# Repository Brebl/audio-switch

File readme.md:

# Audio switch   

This is an avr project for selecting one audio signal from multiple input lines (6-port maximum). The project is designed to minimize power consumption by making use of sleep modes, interrupts and internal timers. Other features include multifunction pushbutton, LCD, SPI-communication, automatic detection of audio signals via ADC.\
Objective for this project is to generate amazing sound with minimal distortion.

## Layout

4-port setup with HD44780 display, installed in 3.5" FDD mounting bracket.\

## Code / operation

Microcontroller unit detects via analog-to-digital converter what audio lines are receiving signal. MCU sends this information through Serial peripheral interface to the primary MCU and based on input port priority, primary MCU switches on correct input port. Port information is shown in LCD. After 10 secs or so, display turn off to save power. Display is accessed using 4-bit interface. Pushbutton can be used to force certain port open or to switch back to automatic operation.
  
In addition to Master, there's 3 git branches. Each for a different version of this project.
- led_version
- display_version
- automatic_version

To get this running you can use a toolchain
```
avr-libc gcc-avr binutils-avr avrdude
```

For to flash your MCU, run
```shell
make fuses
make flash
```

## Hardware  

Primary MCU is Atmel's Attiny4313 MCU, with internal 128 kHz oscillator. ISP programmer needs to be slowed down because of this low power oscillator. (avrdude -B option) Secondary MCU is Attiny24A. Switching is done by 4066B CMOS Quad Bilateral Switch.
This pcb feature a 10-pin male ISP connector for programming/debugging. Powering this device could be made through USB or with 5V regulator you can use for example 9-volt battery. Board is designed using KiCad software.

### Board

Here's my printed circuit board I ordered from a fabricator pcbway.com\

First test setup with "a proper pcb". Works nice.\

### Electrical charecteristics

Voltage: 5V\
Current: 0,11mA\
Audio connection: max 6x stereo in, 1x stereo out

### Roadmap

- [x] Consept testing with Attiny2313A/4313
- [x] Sleep modes, interrupts
- [x] Simple pushbutton logic
- [x] LED interface
- [x] Schematics
- [x] Design PCB & place order
- [x] Board test setup, sound input/output
- [x] Fabricate enclosure
- [x] Power source
- [x] LCD interface
- [X] ATtiny24A with ADC
- [x] SPI communication 
- [x] Automatic audio signal detection
- [x] Multifunction pushbutton
- [ ] Measure distortion

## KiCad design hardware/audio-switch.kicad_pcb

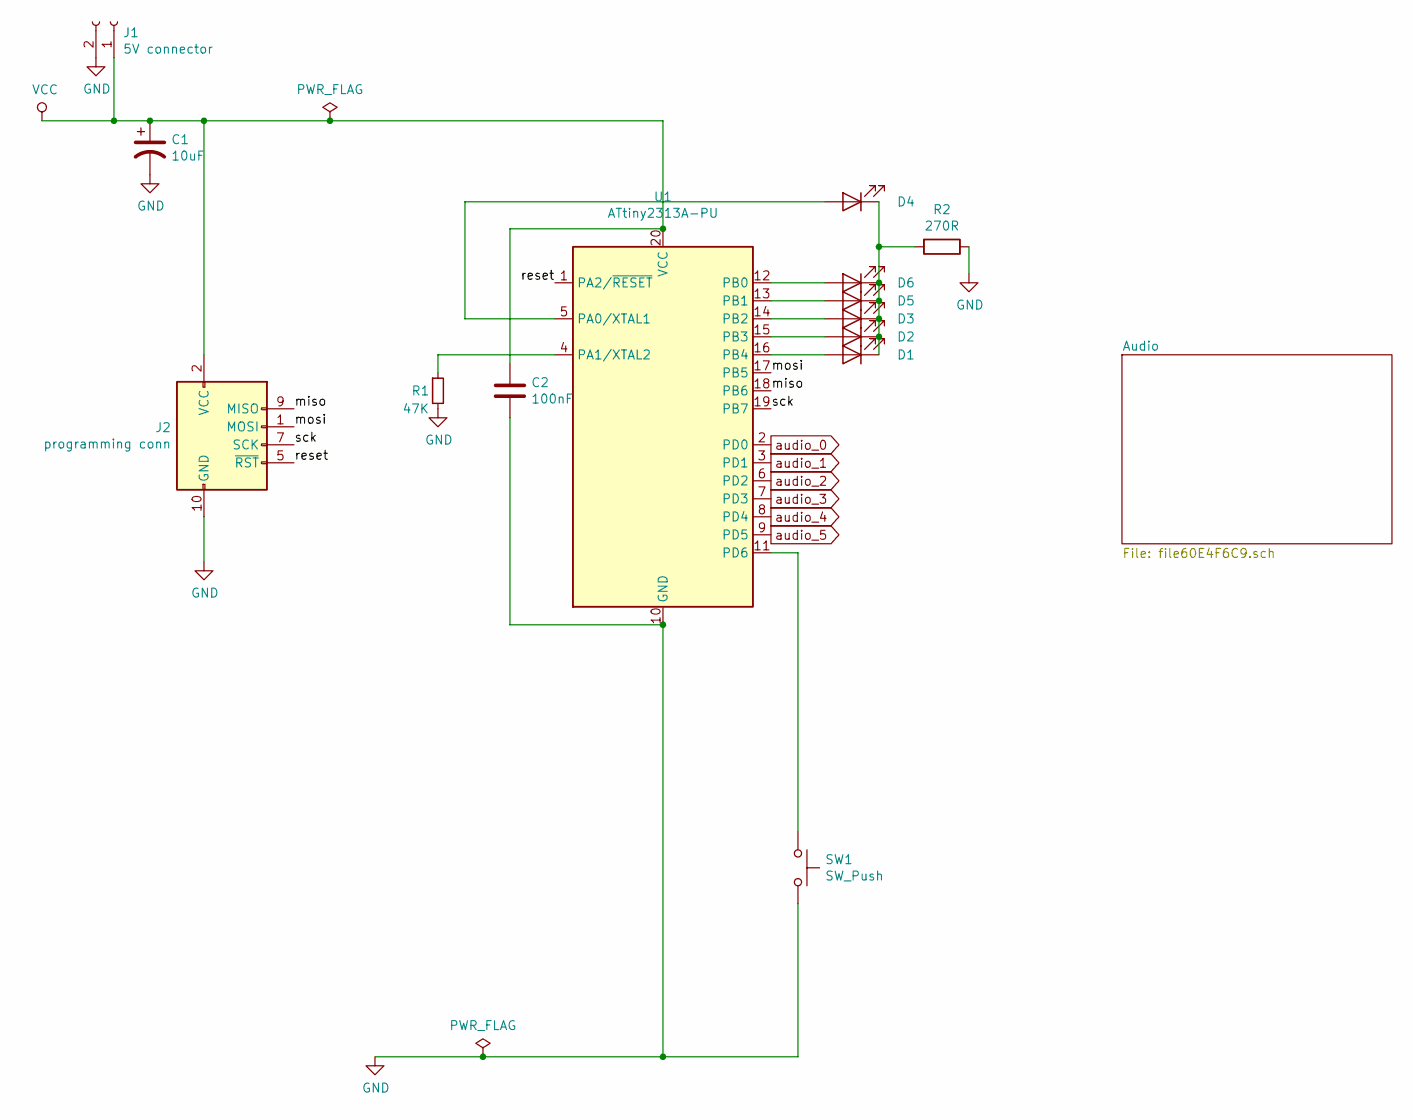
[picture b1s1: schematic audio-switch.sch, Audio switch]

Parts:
C1: 10uF; CP_Radial_D4.0mm_P1.50mm
C2: 100nF; CP_Radial_D5.0mm_P2.00mm
D1, D2, D3, D4, D5, D6: LED; LED_D3.0mm
J1: 5V connector; SolderWirePad_1x02_P3.81mm_Drill1mm
J2: programming conn; PinHeader_2x05_P2.54mm_Vertical
R1: 47K; R_Axial_DIN0207_L6.3mm_D2.5mm_P7.62mm_Horizontal
R2: 270R; R_Axial_DIN0207_L6.3mm_D2.5mm_P7.62mm_Horizontal
SW1: SW_Push; SolderWirePad_1x02_P3.81mm_Drill1mm
U1: ATtiny2313A-PU; DIP-20_W7.62mm

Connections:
/miso: J2.9 (MISO), U1.18 (PB6)
/mosi: J2.1 (MOSI), U1.17 (PB5)
/reset: J2.5 (~RST), U1.1 (PA2/~RESET)
/sck: J2.7 (SCK), U1.19 (PB7)
GND: C1.2, C2.2, J1.2, J2.4 (GND), J2.6 (GND), J2.8 (GND), J2.10 (GND), R1.2, R2.1, SW1.2, U1.10 (GND); also elsewhere on the board
unnamed: D1.1 (K), D2.1 (K), D3.1 (K), D4.1 (K), D5.1 (K), D6.1 (K), R2.2
unnamed: D1.2 (A), U1.16 (PB4)
unnamed: D2.2 (A), U1.15 (PB3)
unnamed: D3.2 (A), U1.14 (PB2)
unnamed: D4.2 (A), U1.5 (PA0/XTAL1)
unnamed: D5.2 (A), U1.13 (PB1)
unnamed: D6.2 (A), U1.12 (PB0)
unnamed: R1.1, U1.4 (PA1/XTAL2)
unnamed: SW1.1, U1.11 (PD6)
VCC: C1.1, C2.1, J1.1, J2.2 (VCC), U1.20 (VCC); also elsewhere on the board
audio_0: U1.2 (PD0); also elsewhere on the board
audio_1: U1.3 (PD1); also elsewhere on the board
audio_2: U1.6 (PD2); also elsewhere on the board
audio_3: U1.7 (PD3); also elsewhere on the board
audio_4: U1.8 (PD4); also elsewhere on the board
audio_5: U1.9 (PD5); also elsewhere on the board

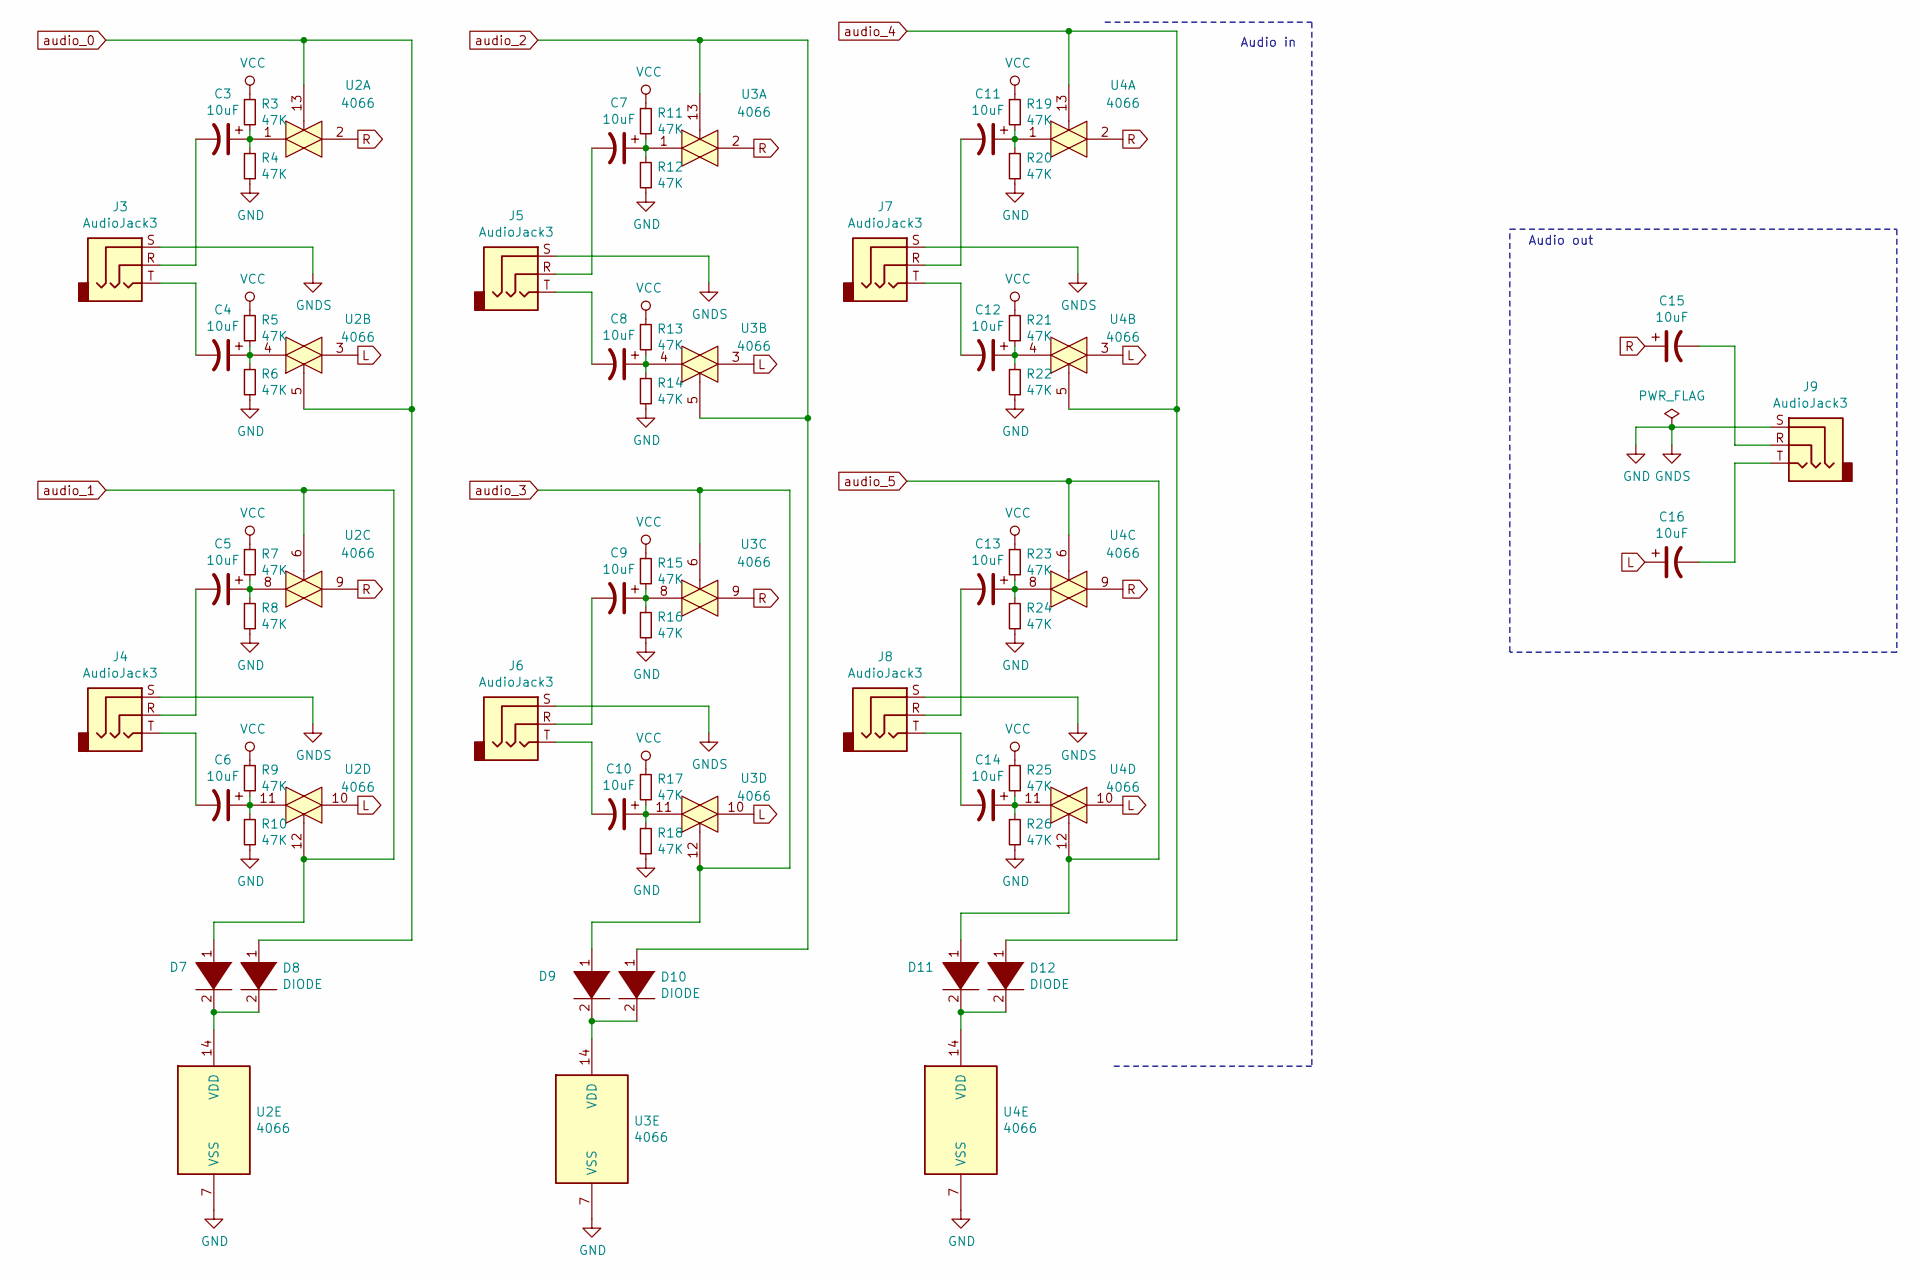
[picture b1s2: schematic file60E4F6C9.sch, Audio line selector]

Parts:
C3, C4, C5, C6, C7, C8, C9, C10, C11, C12, C13, C14, C15, C16: 10uF; CP_Radial_D4.0mm_P1.50mm
D7, D8, D9, D10, D11, D12: DIODE; D_T-1_P5.08mm_Horizontal
J3, J4, J5, J6, J7, J8, J9: AudioJack3; SolderWirePad_1x03_P3.175mm_Drill1mm
R3, R4, R5, R6, R7, R8, R9, R10, R11, R12, R13, R14, R15, R16, R17, R18, R19, R20, R21, R22, R23, R24, R25, R26: 47K; R_Axial_DIN0207_L6.3mm_D2.5mm_P7.62mm_Horizontal
U2, U3, U4: 4066; DIP-14_W7.62mm

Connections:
GND: J3.S, J4.S, J5.S, J6.S, J7.S, J8.S, J9.S, R4.2, R6.2, R8.2, R10.2, R12.2, R14.2, R16.2, R18.2, R20.2, R22.2, R24.2, R26.2, U2.7 (VSS), U3.7 (VSS), U4.7 (VSS); also elsewhere on the board
L: C16.1, U2.3, U2.10, U3.3, U3.10, U4.3, U4.10
unnamed: C3.1, R3.2, R4.1, U2.1
unnamed: C3.2, J3.R
unnamed: C4.1, R5.2, R6.1, U2.4
unnamed: C4.2, J3.T
unnamed: C5.1, R7.2, R8.1, U2.8
unnamed: C5.2, J4.R
unnamed: C6.1, R9.2, R10.1, U2.11
unnamed: C6.2, J4.T
unnamed: C7.1, R11.2, R12.1, U3.1
unnamed: C7.2, J5.R
unnamed: C8.1, R13.2, R14.1, U3.4
unnamed: C8.2, J5.T
unnamed: C9.1, R15.2, R16.1, U3.8
unnamed: C9.2, J6.R
unnamed: C10.1, R17.2, R18.1, U3.11
unnamed: C10.2, J6.T
unnamed: C11.1, R19.2, R20.1, U4.1
unnamed: C11.2, J7.R
unnamed: C12.1, R21.2, R22.1, U4.4
unnamed: C12.2, J7.T
unnamed: C13.1, R23.2, R24.1, U4.8
unnamed: C13.2, J8.R
unnamed: C14.1, R25.2, R26.1, U4.11
unnamed: C14.2, J8.T
unnamed: C15.2, J9.R
unnamed: C16.2, J9.T
unnamed: D7.2 (A), D8.2 (A), U2.14 (VDD)
unnamed: D9.2 (A), D10.2 (A), U3.14 (VDD)
unnamed: D11.2 (A), D12.2 (A), U4.14 (VDD)
R: C15.1, U2.2, U2.9, U3.2, U3.9, U4.2, U4.9
VCC: R3.1, R5.1, R7.1, R9.1, R11.1, R13.1, R15.1, R17.1, R19.1, R21.1, R23.1, R25.1; also elsewhere on the board
audio_0: D8.1 (K), U2.5, U2.13; also elsewhere on the board
audio_1: D7.1 (K), U2.6, U2.12; also elsewhere on the board
audio_2: D10.1 (K), U3.5, U3.13; also elsewhere on the board
audio_3: D9.1 (K), U3.6, U3.12; also elsewhere on the board
audio_4: D12.1 (K), U4.5, U4.13; also elsewhere on the board
audio_5: D11.1 (K), U4.6, U4.12; also elsewhere on the board

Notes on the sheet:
Audio out
Audio in

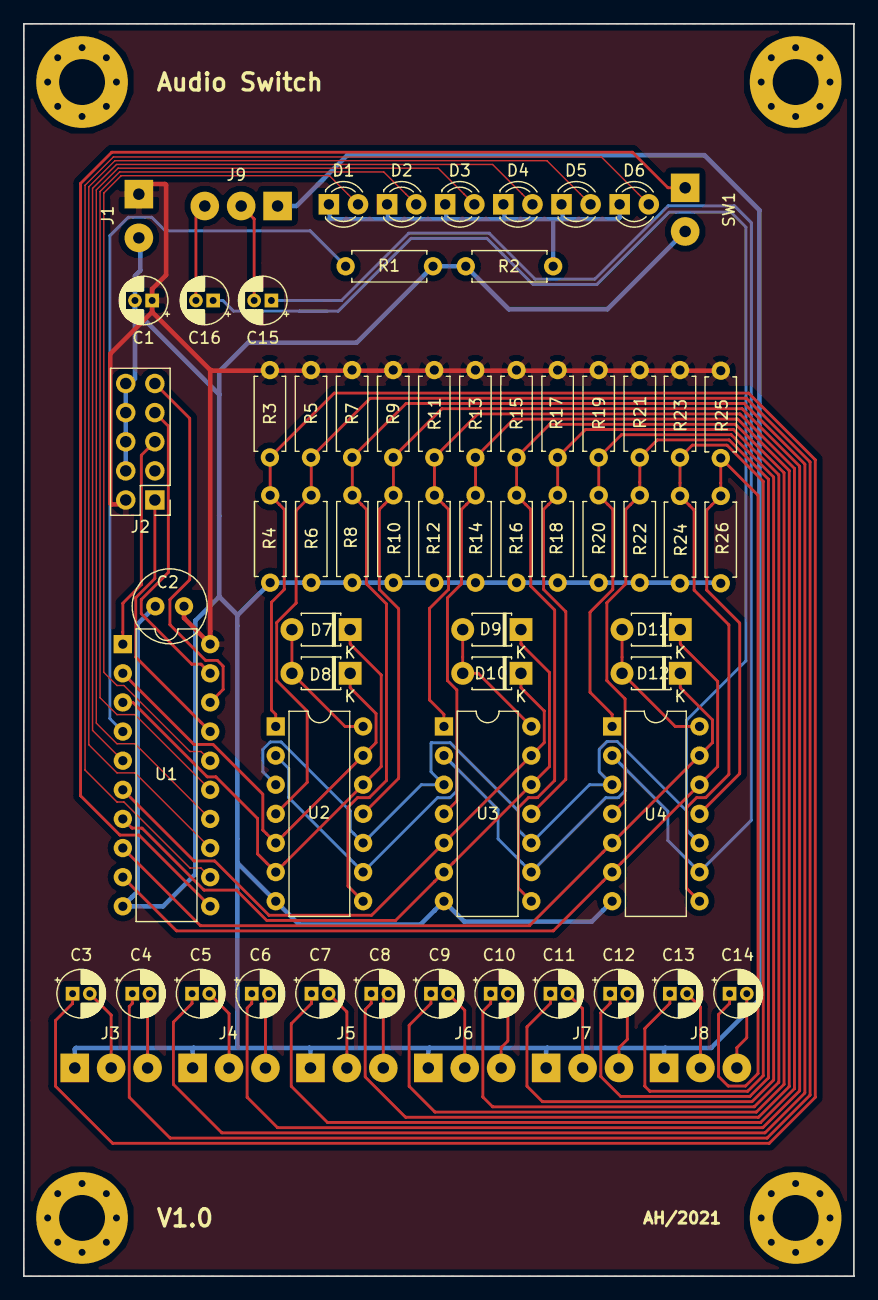
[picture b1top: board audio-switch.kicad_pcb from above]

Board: 2 copper layers, 72.4 x 109.2 mm, 68 parts (0 on the bottom side), 52 nets.

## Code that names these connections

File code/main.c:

#include "main.h" 

int main(void)
{   
    //init ports
    DDRA = (1 << PA0);
    DDRB = (1 << PB0) | (1 << PB1) | (1 << PB2) | (1 << PB3) | (1 << PB4);
    DDRD = (1 << PD0) | (1 << PD1) | (1 << PD2) | (1 << PD3) | (1 << PD4) | (1 << PD5);
    PORTD = (1 << PUSH_BUTTON);
    init_interrupts();

    while (1) {
        sleep_mode();
    }
    return 0;
}

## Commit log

2021-05-30 simplify interrupt
2021-06-01 v0.2
2021-06-03 refactoring
2021-06-04 timeout ok
2021-06-05 initial release
2021-06-06 pwr down
2021-06-06 led max count
2021-06-25 gitignore
2021-06-25 cleanup
2021-06-27 128kHz
2021-06-27 hardware add
2021-09-11 added: TRAN5
2021-11-01 corrected push button pin
2021-11-01 push button interrupt register correct value
2021-11-01 added conf
2021-11-02 use local .conf
2021-11-11 changed main.h to stdint.h
2021-11-11 refactor: buttonpins -> buttonpin
2021-11-13 new files
2021-11-13 overhaul
2021-11-13 folder change
2021-11-13 ditch ld
2021-11-13 remove extra suffixes
2021-11-13 test
2021-11-13 clean
2021-11-14 write version info to eeprom
2021-11-15 change: type name
2021-11-15 changed type name
2021-11-20 moved to corresponding source file
2021-11-20 added: display
2021-11-20 changed: led -> display
2021-11-20 new file
2021-11-20 removed: led
2021-11-20 changed: mcu
2021-11-20 display setup
2021-11-20 changed to display_version
2021-11-20 layout change
2021-11-20 automatic_version
2021-11-23 4bit
2021-11-30 hype
2021-12-05 added: spi sceleton
2021-12-08 added: automatic mode
2021-12-08 volatile enum
2021-12-08 added: automatic mode, multifunction button
